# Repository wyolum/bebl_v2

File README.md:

bebl_v2
=======

"Bar End Brake Light" , redux. v2 of Justin's original BEBL with mods.

License
-------
[CERN Open Hardware Licence v1.2 ]

[CERN Open Hardware Licence v1.2 ]:http://www.ohwr.org/attachments/2388/cern_ohl_v_1_2.txt

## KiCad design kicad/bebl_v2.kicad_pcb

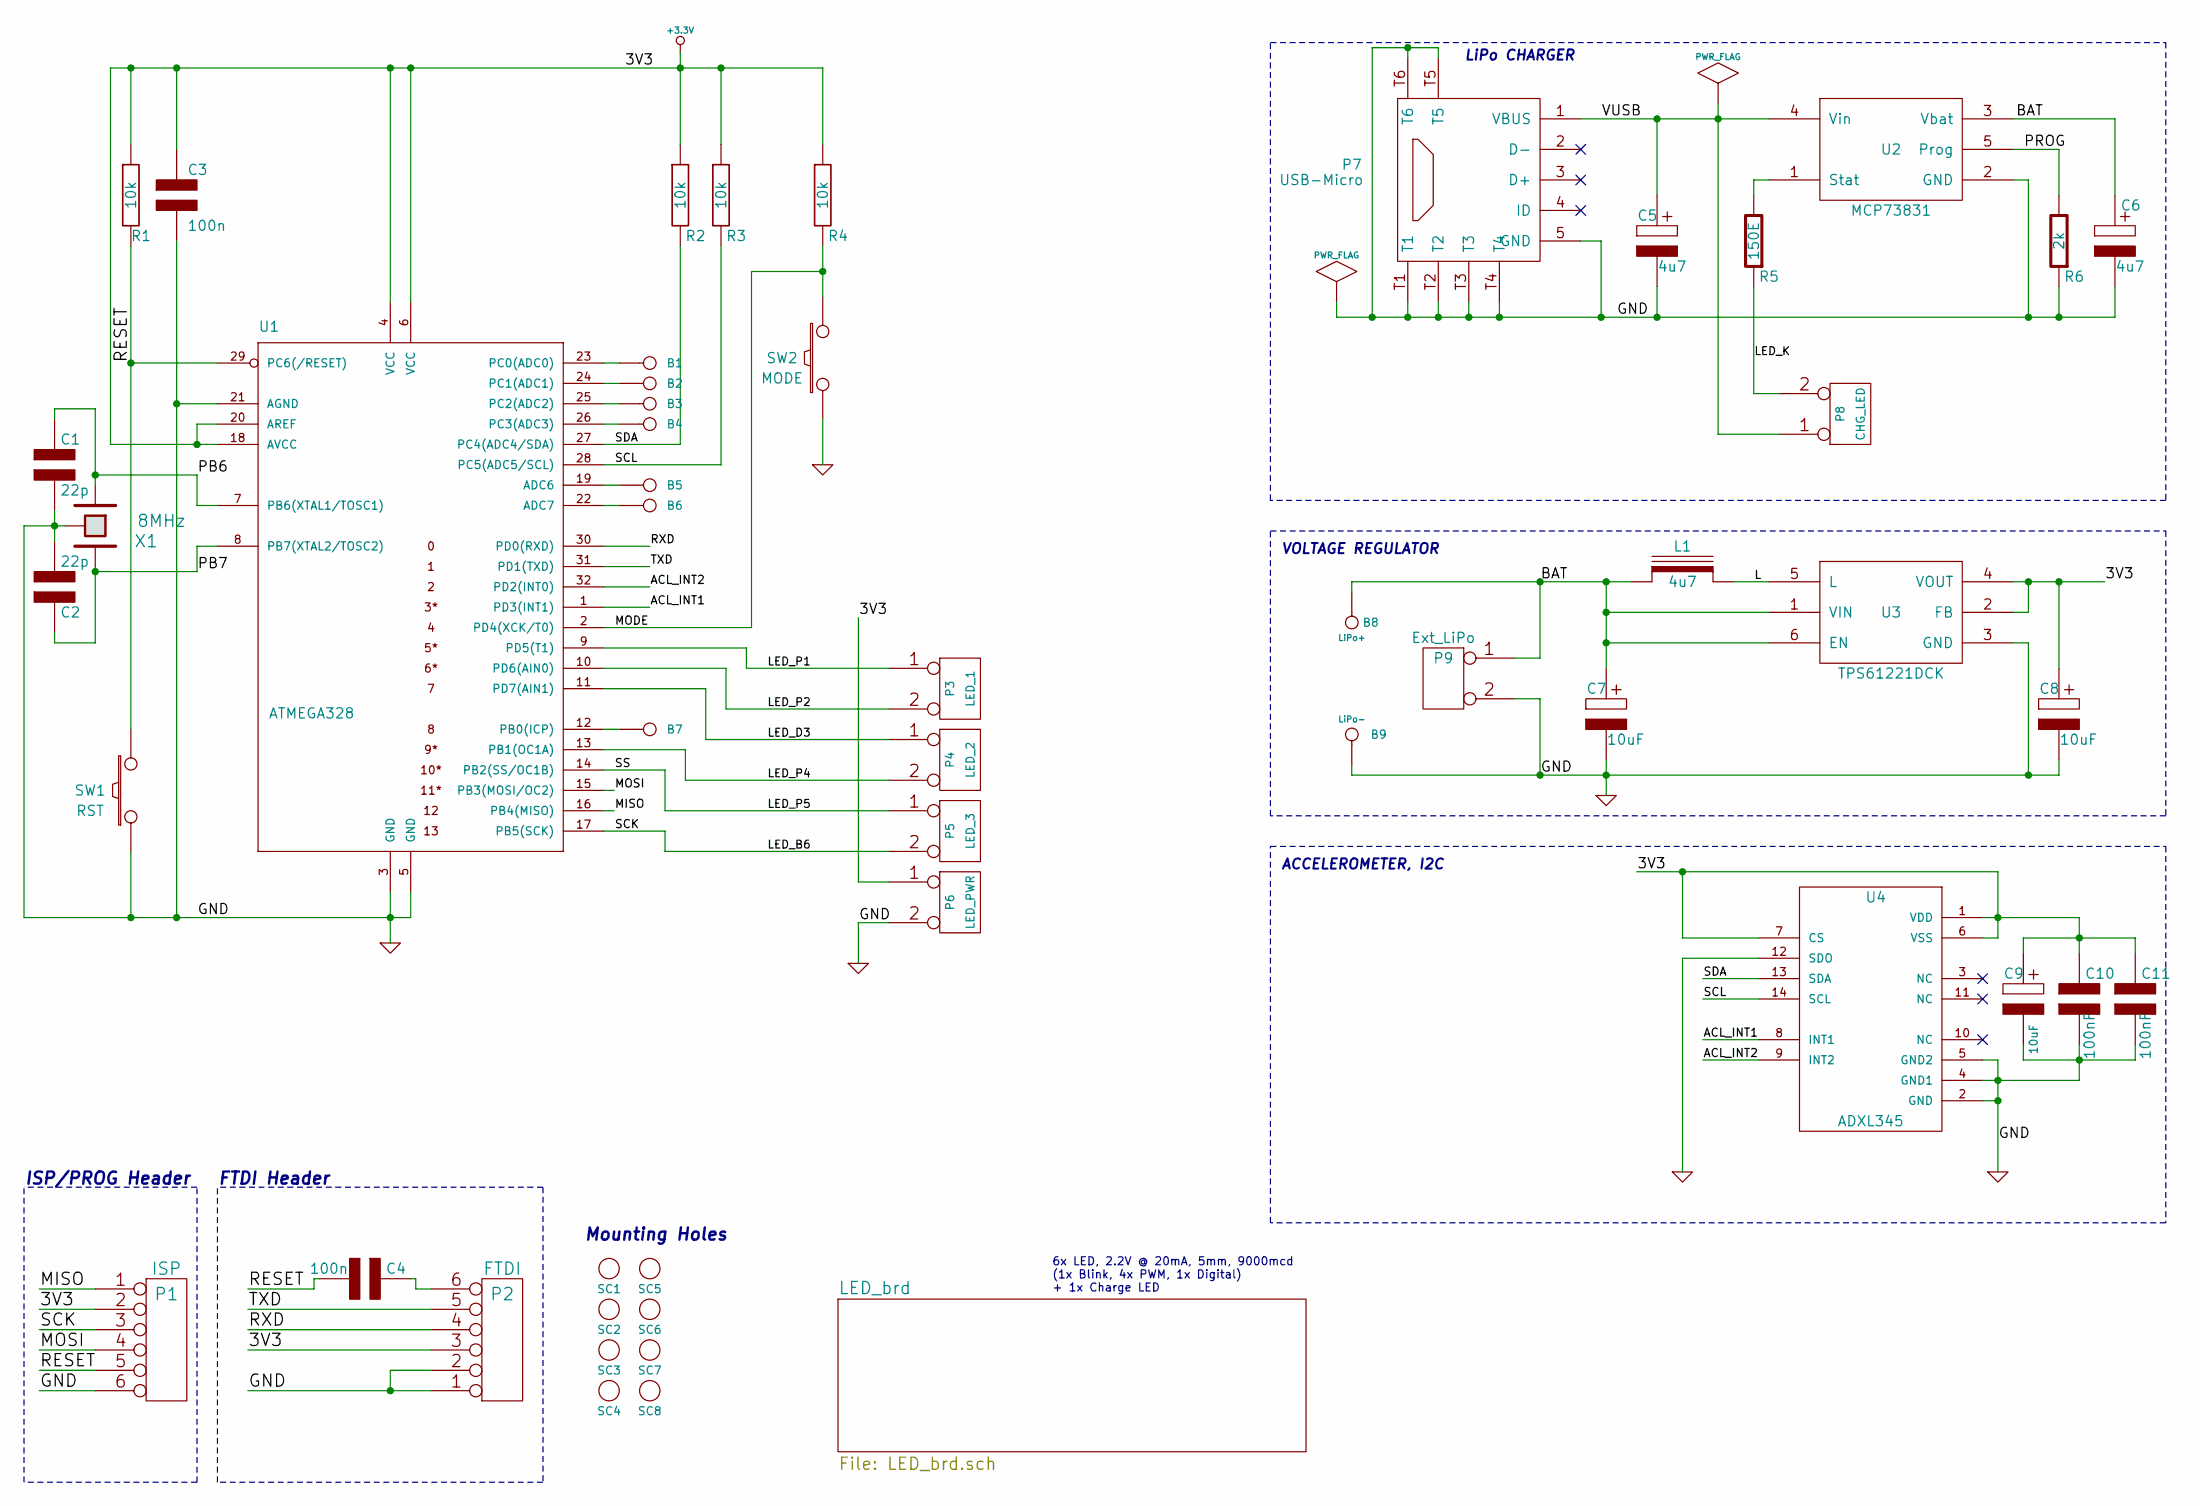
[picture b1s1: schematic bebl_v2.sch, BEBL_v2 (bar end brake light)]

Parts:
B1, B2, B3, B4, B5, B6, B7: I/O; breakout_smd
B8: LiPo+; batt_clip
B9: LiPo-; batt_clip
C1, C2: 22p; c_0805; Digikey 490-1734-1-ND
C3, C4: 100n; c_0805
C5, C6: 4u7; c_0805
C7, C8, C9: 10uF; c_0805
C10, C11: 100nF; c_0805
L1: 4u7; Inductor_LQH3NPN
P1: ISP; Header_3x2_ISP
P2: FTDI; PIN_ARRAY-6X1
P3: LED_1; pin_socket_2
P4: LED_2; pin_socket_2
P5: LED_3; pin_socket_2
P6: LED_PWR; pin_socket_2
P7: USB-Micro; USB_B_Micro
P8: CHG_LED; pin_socket_2
P9: Ext_LiPo; pin_socket_2
R1, R2, R3, R4: 10k; r_0805
R5: 150E; r_0805
R6: 2k; r_0805
SC1, SC2, SC3, SC4, SC5, SC6, SC7, SC8: SCREW; screw_3mm
SW1: RST; Switch_SMT
SW2: MODE; Switch_SMT
U1: ATMEGA328; TQFP32
U2: MCP73831; SOT23-5
U3: TPS61221DCK; SOT23-6_LDO
U4: ADXL345
X1: 8MHz; Xtal_SMD4

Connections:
+3.3V: C3.1, C8.1, C9.1, C10.1, C11.1, P1.2, P2.3, P6.1, R1.1, R2.1, R3.1, R4.1, U1.4 (VCC), U1.6 (VCC), U1.18 (AVCC), U1.20 (AREF), U3.2 (FB), U3.4 (VOUT), U4.1 (VDD), U4.6 (VSS), U4.7 (CS)
/ACL_INT1: U1.1 (PD3(INT1)), U4.8 (INT1)
/ACL_INT2: U1.32 (PD2(INT0)), U4.9 (INT2)
/BAT: B8.1, C6.1, C7.1, L1.1, P9.1, U2.3 (Vbat), U3.1 (VIN), U3.6 (EN)
/L: L1.2, U3.5 (L)
/LED_B6: P1.3, P5.2 (PM), U1.17 (PB5(SCK))
/LED_D3: P4.1, U1.11 (PD7(AIN1))
/LED_K: P8.2 (PM), R5.1
/LED_P1: P3.1, U1.9 (PD5(T1))
/LED_P2: P3.2 (PM), U1.10 (PD6(AIN0))
/LED_P4: P4.2 (PM), U1.13 (PB1(OC1A))
/LED_P5: P5.1, U1.14 (PB2(SS/OC1B))
/MISO: P1.1, U1.16 (PB4(MISO))
/MODE: R4.2, SW2.2, U1.2 (PD4(XCK/T0))
/MOSI: P1.4, U1.15 (PB3(MOSI/OC2))
/PB6: C1.1, U1.7 (PB6(XTAL1/TOSC1)), X1.1
/PROG: R6.2, U2.5 (Prog)
/RESET: C4.2, P1.5, R1.2, SW1.2, U1.29 (PC6(/RESET))
/RXD: P2.4, U1.30 (PD0(RXD))
/SCL: R3.2, U1.28 (PC5(ADC5/SCL)), U4.14 (SCL)
/SDA: R2.2, U1.27 (PC4(ADC4/SDA)), U4.13 (SDA)
/TXD: P2.5, U1.31 (PD1(TXD))
/VUSB: C5.1, P7.1 (VBUS), P8.1, U2.4 (Vin)
unnamed: B1.1, U1.23 (PC0(ADC0))
unnamed: B2.1, U1.24 (PC1(ADC1))
unnamed: B3.1, U1.25 (PC2(ADC2))
unnamed: B4.1, U1.26 (PC3(ADC3))
unnamed: B5.1, U1.19 (ADC6)
unnamed: B6.1, U1.22 (ADC7)
unnamed: B7.1, U1.12 (PB0(ICP))
unnamed: C4.1, P2.6
unnamed: R5.2, U2.1 (Stat)

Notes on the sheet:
FTDI Header
ISP/PROG Header
Mounting Holes
ACCELEROMETER, I2C
VOLTAGE REGULATOR
LiPo CHARGER
6x LED, 2.2V @ 20mA, 5mm, 9000mcd (1x Blink, 4x PWM, 1x Digital) + 1x Charge LED

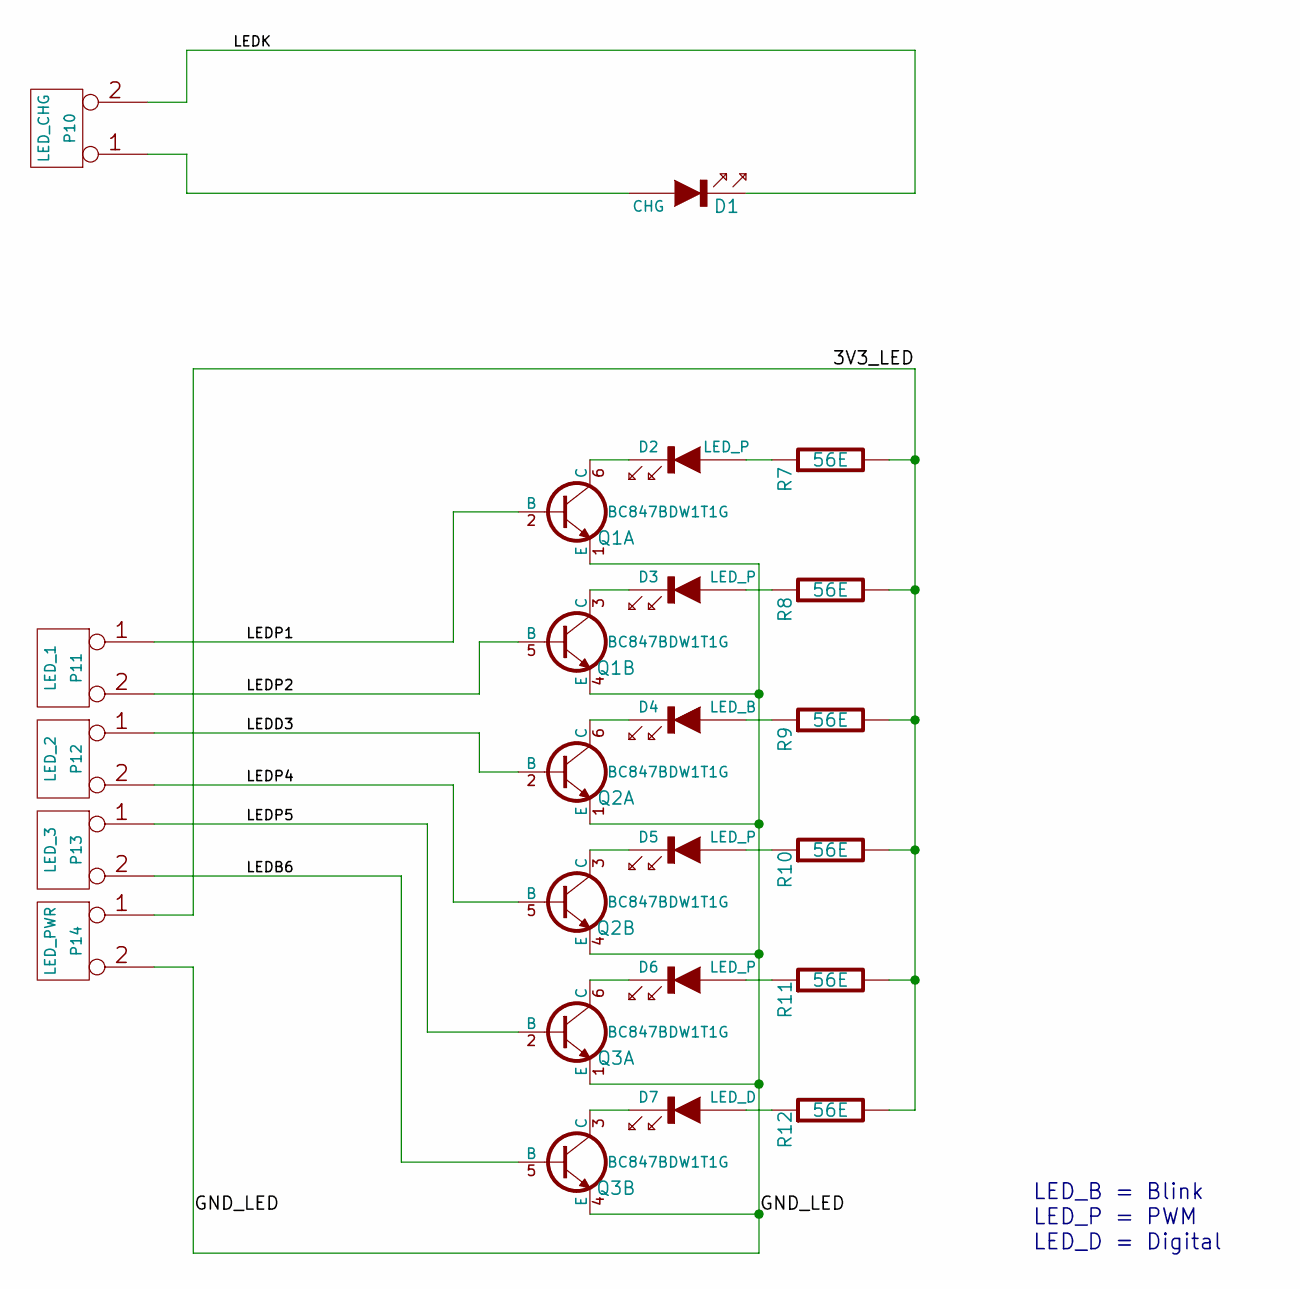
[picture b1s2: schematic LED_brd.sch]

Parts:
D1: CHG; LED-0805
D2, D3, D5, D6: LED_P; LED-5MM
D4: LED_B; LED-5MM
D7: LED_D; LED-5MM
P10: LED_CHG; pin_strip_2
P11: LED_1; pin_strip_2
P12: LED_2; pin_strip_2
P13: LED_3; pin_strip_2
P14: LED_PWR; pin_strip_2
Q1, Q2, Q3: BC847BDW1T1G; SOT23-6
R7, R8, R9, R10, R11, R12: 56E; r_0805

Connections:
/LED_brd/3V3_LED: P14.1, R7.2, R8.2, R9.2, R10.2, R11.2, R12.2
/LED_brd/GND_LED: P14.2 (PM), Q1.1 (E), Q1.4 (E), Q2.1 (E), Q2.4 (E), Q3.1 (E), Q3.4 (E)
/LED_brd/LEDB6: P13.2 (PM), Q3.5 (B)
/LED_brd/LEDD3: P12.1, Q2.2 (B)
/LED_brd/LEDK: D1.2 (K), P10.2 (PM)
/LED_brd/LEDP1: P11.1, Q1.2 (B)
/LED_brd/LEDP2: P11.2 (PM), Q1.5 (B)
/LED_brd/LEDP4: P12.2 (PM), Q2.5 (B)
/LED_brd/LEDP5: P13.1, Q3.2 (B)
unnamed: D1.1 (A), P10.1
unnamed: D2.1 (A), R7.1
unnamed: D2.2 (K), Q1.6 (C)
unnamed: D3.1 (A), R8.1
unnamed: D3.2 (K), Q1.3 (C)
unnamed: D4.1 (A), R9.1
unnamed: D4.2 (K), Q2.6 (C)
unnamed: D5.1 (A), R10.1
unnamed: D5.2 (K), Q2.3 (C)
unnamed: D6.1 (A), R11.1
unnamed: D6.2 (K), Q3.6 (C)
unnamed: D7.1 (A), R12.1
unnamed: D7.2 (K), Q3.3 (C)

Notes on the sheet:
LED_B = Blink LED_P = PWM LED_D = Digital

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
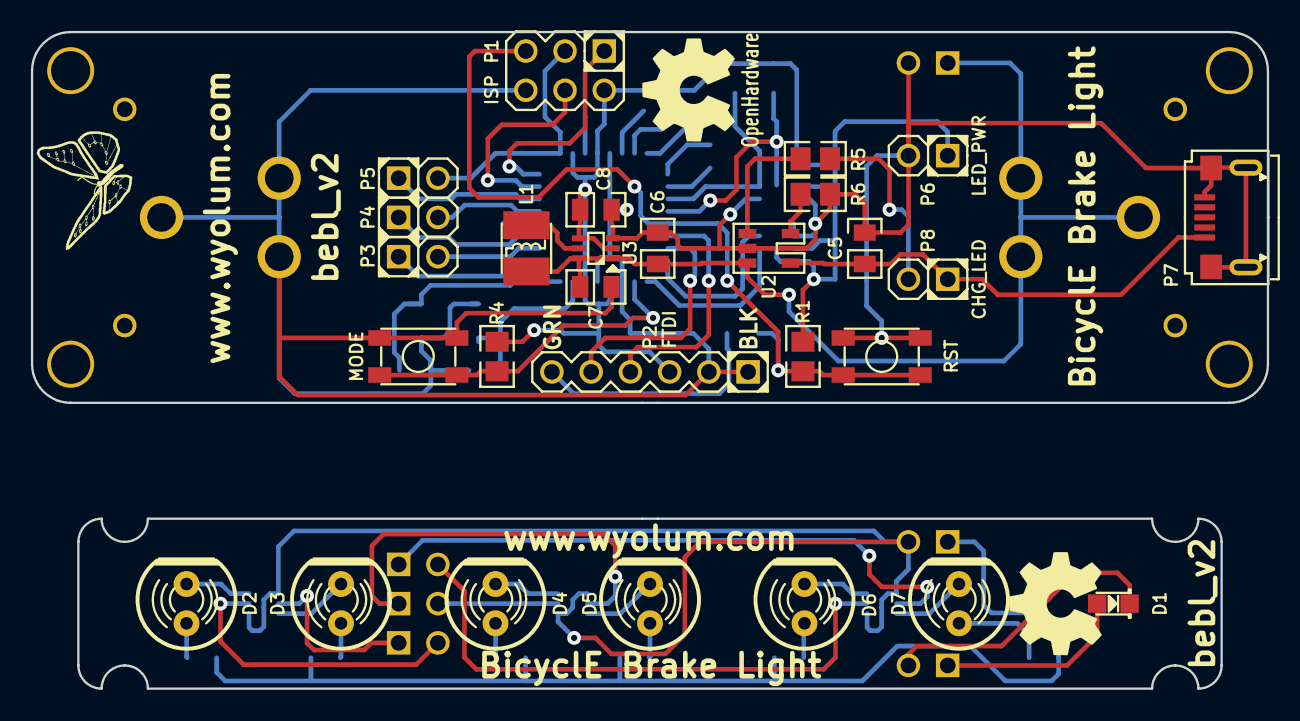
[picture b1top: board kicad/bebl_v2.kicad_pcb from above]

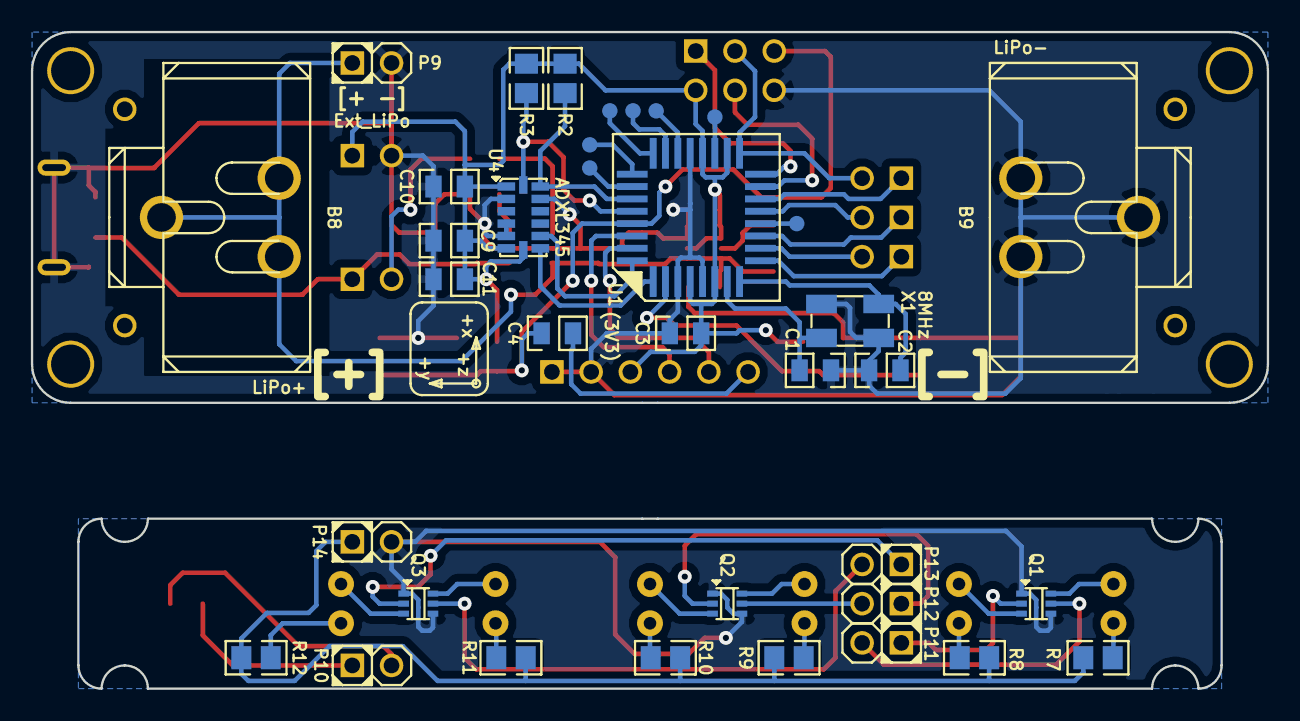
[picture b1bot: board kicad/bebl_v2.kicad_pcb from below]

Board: 2 copper layers, 80.0 x 42.5 mm, 73 parts (36 on the bottom side), 56 nets.

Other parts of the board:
G1: Logo-WL3

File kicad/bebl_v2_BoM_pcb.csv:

"Id";"Designator";"Package";"Quantity";"Designation";"Supplier and ref";
1;"P10";"pin_strip_2";1;"LED_CHG";;;
2;"P8";"pin_socket_2";1;"CHG_LED";;;
3;"P12";"pin_strip_2";1;"LED_2";;;
4;"P14";"pin_strip_2";1;"LED_PWR";;;
5;"P4";"pin_socket_2";1;"LED_2";;;
6;"P3";"pin_socket_2";1;"LED_1";;;
7;"SC8,SC7,SC6,SC5,SC1,SC2,SC3,SC4";"screw_3mm";8;"SCREW";;;
8;"R8,R7,R9,R10,R11,R12";"r_0805";6;"22E";;;
9;"C1,C2";"c_0805";2;"22p";;;
10;"C3,C4";"c_0805";2;"100n";;;
11;"C7,C9,C8";"c_0805";3;"10uF";;;
12;"C5,C6";"c_0805";2;"4u7";;;
13;"C11,C10";"c_0805";2;"100nF";;;
14;"D7";"LED-5MM";1;"LED_B";;;
15;"D6,D5,D3,D2";"LED-5MM";4;"LED_P";;;
16;"D4";"LED-5MM";1;"LED_D";;;
17;"D1";"LED-0805";1;"CHG";;;
18;"L1";"Inductor_LQH3NPN";1;"4u7";;;
19;"P2";"PIN_ARRAY-6X1";1;"FTDI";;;
20;"R4,R2,R3,R1";"r_0805";4;"10k";;;
21;"R5";"r_0805";1;"150E";;;
22;"R6";"r_0805";1;"2k";;;
23;"SW1";"Switch_SMT";1;"RST";;;
24;"U1";"TQFP32";1;"ATMEGA328";;;
25;"U4";"ADXL345";1;"ADXL345";;;
26;"U3";"SOT23-6_LDO";1;"TPS61221DCK";;;
27;"X1";"Xtal_SMD4";1;"8MHz";;;
28;"B1,B2,B3,B4,B5,B6,B7";"breakout_smd";7;"I/O";;;
29;"P1";"Header_3x2_ISP";1;"ISP";;;
30;"P5";"pin_socket_2";1;"LED_3";;;
31;"P6";"pin_socket_2";1;"LED_PWR";;;
32;"P9";"pin_socket_2";1;"Ext_LiPo";;;
33;"P13";"pin_strip_2";1;"LED_3";;;
34;"P11";"pin_strip_2";1;"LED_1";;;
35;"SW2";"Switch_SMT";1;"MODE";;;
36;"G***,G***";"OSHW_6mm";2;"LOGO";;;
37;"G1";"Logo-WL3";1;"Logo-WL3";;;
38;"U2";"SOT23-5";1;"MCP73831";;;
39;"Q1,Q2,Q3";"SOT363";3;"BC847BDW1T1G";;;
40;"B9";"batt_clip";1;"LiPo-";;;
41;"B8";"batt_clip";1;"LiPo+";;;
42;"P7";"USB_B_Micro_seeed";1;"USB-Micro";;;

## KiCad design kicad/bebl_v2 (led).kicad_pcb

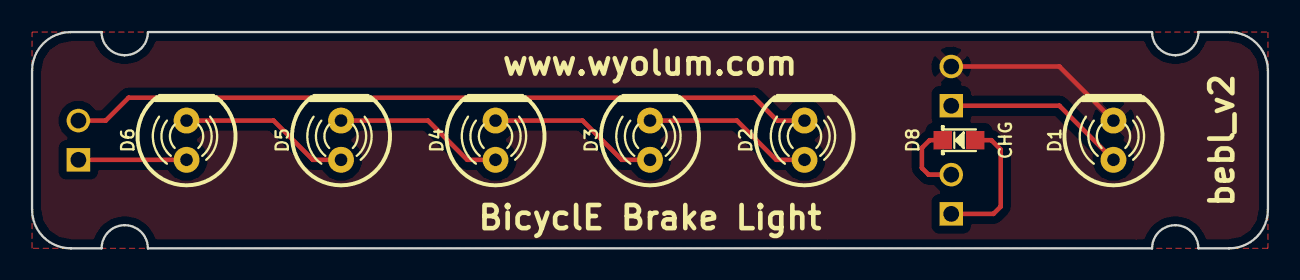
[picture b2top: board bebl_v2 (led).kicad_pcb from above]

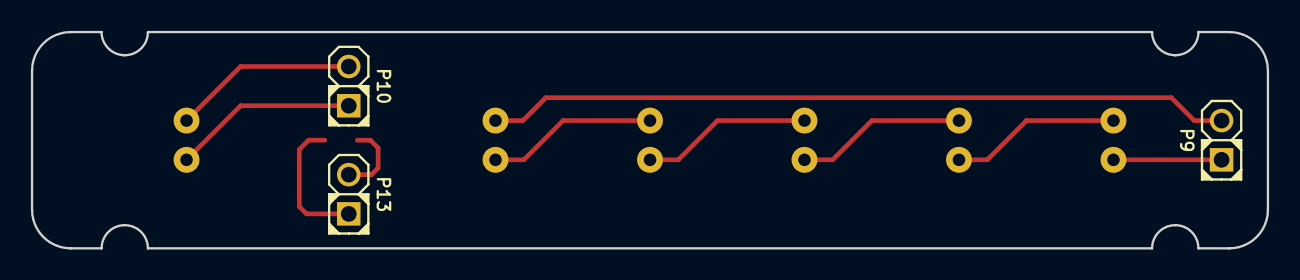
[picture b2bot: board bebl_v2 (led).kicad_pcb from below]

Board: 2 copper layers, 80.0 x 14.0 mm, 10 parts (3 on the bottom side), 10 nets.

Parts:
D1: DRL; LED-5MM
D2, D3, D4, D5, D6: LED_R; LED-5MM
D8: CHG; LED-0805
P9: LED_DRV; pin_strip_2
P10: LED_DRL; pin_strip_2
P13: LED_CHG; pin_strip_2

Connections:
/ANOD: D6.1, P9.1
/CATH: D2.2, P9.2
/D1A: D1.1, P10.1
/D1K: D1.2, P10.2
unnamed: D2.1, D3.2
unnamed: D3.1, D4.2
unnamed: D4.1, D5.2
unnamed: D5.1, D6.2
unnamed: D8.1, P13.1
unnamed: D8.2, P13.2

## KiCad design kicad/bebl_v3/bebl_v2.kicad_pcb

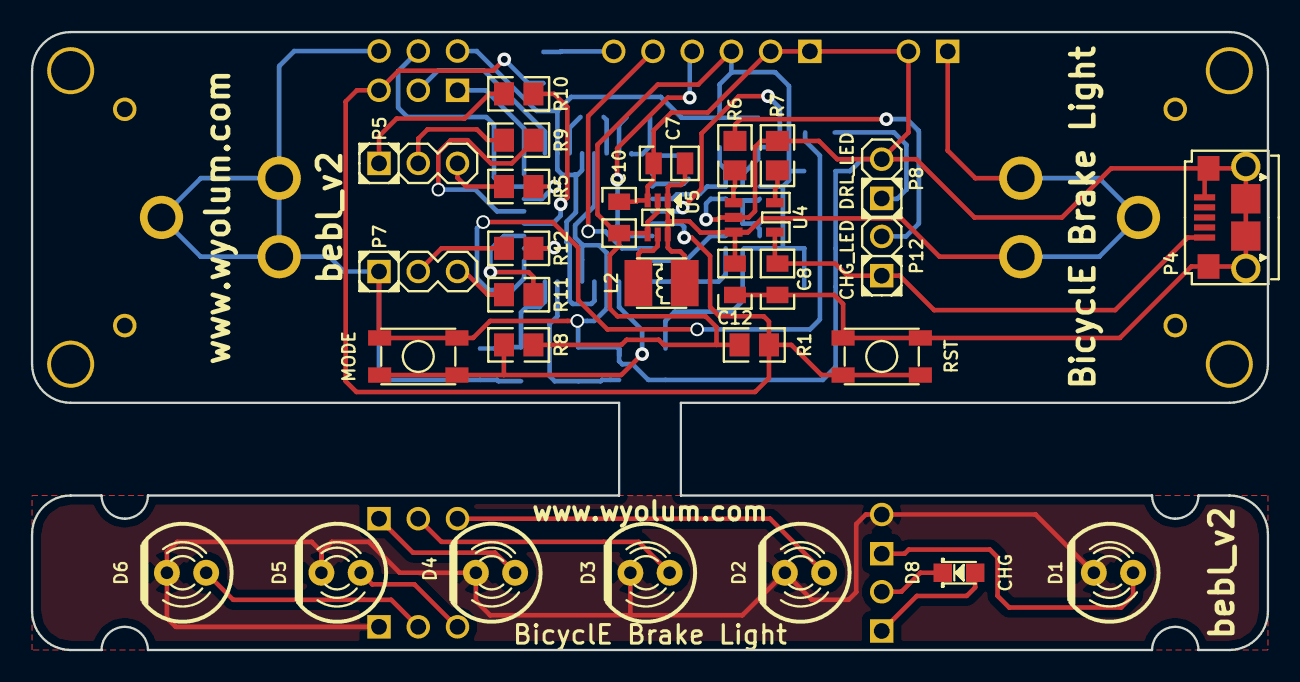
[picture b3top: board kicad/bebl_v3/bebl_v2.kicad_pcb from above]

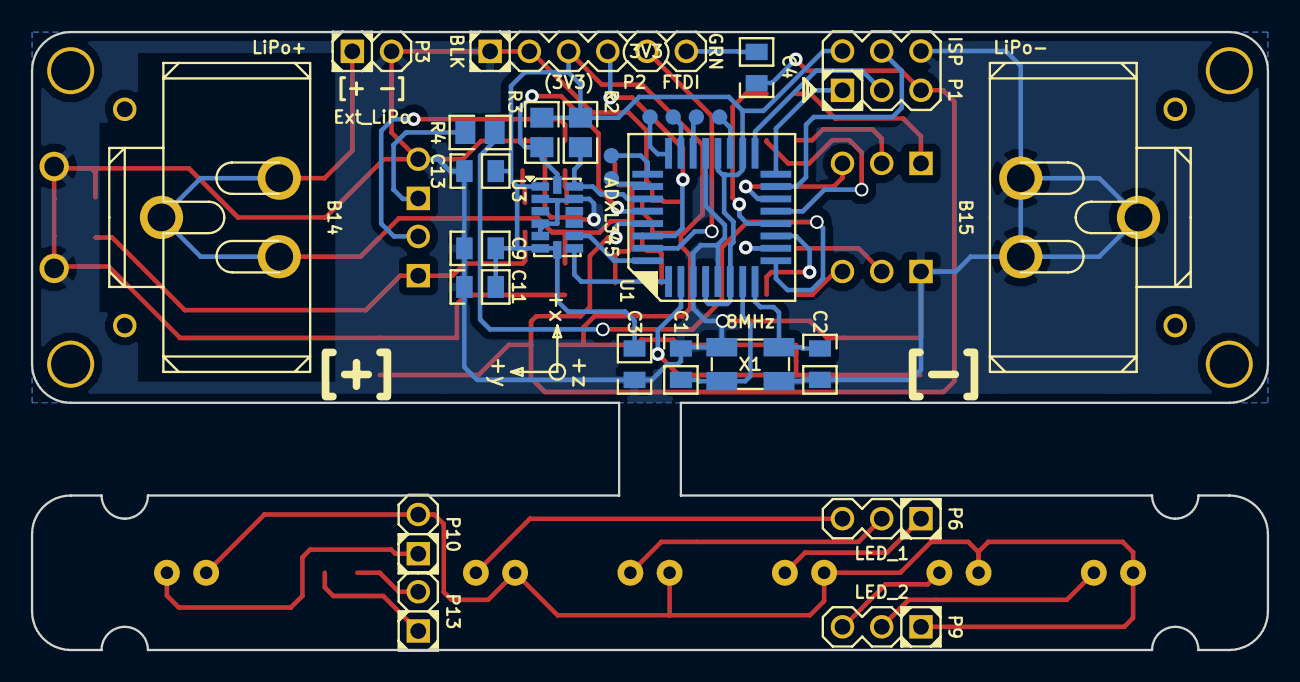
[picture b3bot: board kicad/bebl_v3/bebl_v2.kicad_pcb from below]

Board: 2 copper layers, 80.0 x 40.0 mm, 66 parts (28 on the bottom side), 49 nets.

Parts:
B1, B2, B3, B4, B5, B6: I/O; breakout_smd
B14: LiPo+; batt_clip
B15: LiPo-; batt_clip
C1, C2: 22p; c_0805
C3, C4: 100n; c_0805
C7, C9, C10: 10uF; c_0805
C8, C12: 4u7; c_0805
C11, C13: 100nF; c_0805
D1: DRL; LED-5MM
D2, D3, D4, D5, D6: LED_R; LED-5MM
D8: CHG; LED-0805
L2: 4u7; Inductor_LQH3NPN
P1: ISP; Header_3x2_ISP
P2: FTDI; PIN_ARRAY-6X1
P3: Ext_LiPo; pin_strip_2
P4: USB-Micro; USB_B_Micro
P5: DRV_1; pin_socket_3
P6: LED_1; PIN_ARRAY-3X1
P7: DRV_2; pin_socket_3
P8: DRL_LED; pin_socket_2
P9: LED_2; PIN_ARRAY-3X1
P10: LED_DRL; pin_strip_2
P12: CHG_LED; pin_socket_2
P13: LED_CHG; pin_strip_2
R1, R2, R3, R8: 10k; r_0805
R4, R5, R9, R10, R11, R12: 55E; r_0805
R6: 150E; r_0805
R7: 2k; r_0805
SC1, SC2, SC3, SC4, SC5, SC6, SC7, SC8: SCREW; screw_3mm
SW1: RST; Switch_SMT
SW2: MODE; Switch_SMT
U1: ATMEGA328; TQFP32
U3: ADXL345
U4: MCP73831; SOT23-5
U5: TPS61221DCK; SOT23-6_LDO
X1: 8MHz; Xtal_SMD4

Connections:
+3.3V: C3.1, C9.1, C10.1, C11.1, C13.1, P1.2, P2.3, R1.1, R2.1, R3.1, R8.1, U1.4, U1.6, U1.18, U1.20, U3.1, U3.6, U3.7, U5.2, U5.4
/ACL_INT1: U1.1, U3.8
/ACL_INT2: U1.32, U3.9
/BAT: B14.1, C7.1, C12.1, L2.1, P3.1, U4.3, U5.1, U5.6
/D1A: D1.1, P10.1
/DRL: P8.1, R4.1
/L: L2.2, U5.5
/LED_D1: R4.2, U1.9
/LED_D2: R5.2, U1.14
/LED_D3: R9.2, U1.13
/LED_D4: R10.2, U1.12
/LED_D5: R11.2, U1.11
/LED_D6: R12.2, U1.10
/LED_GND: D1.2, D2.2, D3.2, D4.2, D5.2, D6.2, P9.1, P10.2
/MISO: P1.1, U1.16
/MODE: R8.2, SW2.2, U1.2
/MOSI: P1.4, U1.15
/PB6: C1.1, U1.7, X1.1
/PB7: C2.2, U1.8, X1.2
/PROG: R7.2, U4.5
/RESET: C4.2, P1.5, R1.2, SW1.2, U1.29
/RXD: P2.4, U1.30
/SCK: P1.3, U1.17
/SCL: R3.2, U1.28, U3.14
/SDA: R2.2, U1.27, U3.13
/TXD: P2.5, U1.31
/VUSB: C8.1, P4.1, P12.1, U4.4
GND: B15.1, C1.2, C2.1, C3.2, C7.2, C8.2, C9.2, C10.2, C11.2, C12.2, C13.2, P1.6, P2.1, P2.2, P3.2, P4.5, P4.T1, P4.T2, P4.T3, P4.T4, P4.T5, P4.T6, P7.1, P8.2, R7.1, SW1.1, SW2.1, U1.3, U1.5, U1.21, U3.2, U3.4, U3.5, U3.12, U4.2, U5.3, X1.3
unnamed: B1.1, U1.23
unnamed: B2.1, U1.24
unnamed: B3.1, U1.25
unnamed: B4.1, U1.26
unnamed: B5.1, U1.19
unnamed: B6.1, U1.22
unnamed: C4.1, P2.6
unnamed: D2.1, P6.3
unnamed: D3.1, P6.2
unnamed: D4.1, P6.1
unnamed: D5.1, P9.3
unnamed: D6.1, P9.2
unnamed: D8.1, P13.1
unnamed: D8.2, P13.2
unnamed: P5.1, R10.1
unnamed: P5.2, R9.1
unnamed: P5.3, R5.1
unnamed: P7.2, R12.1
unnamed: P7.3, R11.1
unnamed: P12.2, R6.1
unnamed: R6.2, U4.1

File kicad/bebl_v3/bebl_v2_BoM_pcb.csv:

Id,Designator,Package,Quantity,Designation,Supplier and ref
1,B14,bebl_v2_pretty:batt_clip,1,LiPo+,
2,B15,bebl_v2_pretty:batt_clip,1,LiPo-,
3,P13,bebl_v2_pretty:pin_strip_2,1,LED_CHG,
4,P12,bebl_v2_pretty:pin_socket_2,1,CHG_LED,
5,P9,bebl_v2_pretty:pin_strip_2,1,LED_DRV,
6,P10,bebl_v2_pretty:pin_strip_2,1,LED_DRL,
7,P11,bebl_v2_pretty:pin_socket_2,1,DRV_LED,
8,P8,bebl_v2_pretty:pin_socket_2,1,DRL_LED,
9,"SC8,SC7,SC6,SC5,SC1,SC2,SC3,SC4",bebl_v2_pretty:screw_3mm,8,SCREW,
10,SW2,bebl_v2_pretty:Switch_SMT,1,MODE,
11,"R8,R1,R2,R3",bebl_v2_pretty:r_0805,4,10k,RMCF0805FT10K0CT-ND
12,"C1,C2",bebl_v2_pretty:c_0805,2,22p,
13,"C3,C4",bebl_v2_pretty:c_0805,2,100n,CL21B104KACNNNC
14,"C5,C7,C9,C10",bebl_v2_pretty:c_0805,4,10uF,
15,C6,bebl_v2_pretty:c_0805,1,1uF,
16,"C8,C12",bebl_v2_pretty:c_0805,2,4u7,
17,"C11,C13",bebl_v2_pretty:c_0805,2,100nF,
18,D1,bebl_v2_pretty:LED-5MM,1,DRL,
19,"D2,D3,D4,D5,D6",bebl_v2_pretty:LED-5MM,5,LED_R,
20,D7,bebl_v2_pretty:Diode-EMD2,1,RB520S-30TE61,
21,D8,bebl_v2_pretty:LED-0805,1,CHG,
22,L1,bebl_v2_pretty:Inductor_NLCV32,1,10uH,
23,L2,bebl_v2_pretty:Inductor_LQH3NPN,1,4u7,
24,P2,bebl_v2_pretty:PIN_ARRAY-6X1,1,FTDI,
25,P4,bebl_v2_pretty:USB_B_Micro,1,USB-Micro,
26,R4,bebl_v2_pretty:r_0805,1,140E,
27,R5,bebl_v2_pretty:r_0805,1,12.4E,
28,R6,bebl_v2_pretty:r_0805,1,150E,
29,R7,bebl_v2_pretty:r_0805,1,2k,
30,SW1,bebl_v2_pretty:Switch_SMT,1,RST,
31,U1,bebl_v2_pretty:TQFP32,1,ATMEGA328,ATMEGA328P-AU
32,U2,bebl_v2_pretty:SOT23-6,1,FAN5346,
33,U3,bebl_v2_pretty:ADXL345,1,ADXL345,
34,U4,bebl_v2_pretty:SOT23-5,1,MCP73831,
35,U5,bebl_v2_pretty:SOT23-6_LDO,1,TPS61221DCK,
36,X1,bebl_v2_pretty:Xtal_SMD4,1,8MHz,
37,P3,bebl_v2_pretty:pin_strip_2,1,Ext_LiPo,
38,"B1,B2,B3,B4,B5,B6,B10,B11,B12,B13",bebl_v2_pretty:breakout_smd,10,I/O,
39,P1,bebl_v2_pretty:Header_3x2_ISP,1,ISP,

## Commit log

2014-09-14 bebl_v2 initial commit
2014-09-14 bebl_v2 work in progress
2014-10-13 LED driver reference circuits added
2014-10-21 work in progress
2014-10-26 bebl_v2 initial 3d mockup
2014-10-27 bebl_v2 3d mockup of 2 separate boards
2014-10-28 working on case for bebl_v2
2014-10-28 bebl_v2 3d of housing, work in progress
2014-10-29 bebl_v2 track layout, work in progress
2014-10-30 bebl_v2 track layout, almost done
2014-10-30 created new wedge piece with SP cutout.
2014-10-30 jwedge update
2014-10-31 minor tweeks to jwedge
2014-11-01 bebl_v2 box stl files ready for prototype
2014-11-02 made an alternative back cover that does not need to be transparent
2014-11-03 modified justins version of top cover
2014-11-03 fixed led placement
2014-11-03 fixed jcover fillet_r and led placement
2014-11-03 bebl_v2 added new lens cover
2014-11-03 bebl_v2 minor update
2014-11-04 changed fillet radius on jwedge
2014-11-11 minor update
2014-11-13 BoM modified
2014-11-14 direct LED drive version, work in progress
2014-11-15 revised layout for driverless version, in folder bebl_v3. Work in progress
2014-11-16 revised layout for driverless version, in folder bebl_v3. Check PDF files in GERBER folder
2014-11-16 modified housing drawing
2014-11-18 corrected accel x/y/z markings on silk legend
2014-12-04 working on transistor based driver for leds
2014-12-05 modified schematic for transistor drive
2014-12-10 minor cleanup
2014-12-15 new LED drive circuit, work in progress
2015-01-26 making some progress with new layout
2015-01-29 layout work in progress
2015-01-30 track layout done. Needs verification
2015-01-31 added Justin's local path for 3D files
2015-02-02 made LED board smaller
2015-02-03 bebl_v2 gerbers ready. BoM pending
2015-02-03 footprint errors corrected, BoM ready, but pending seeed format
2015-02-04 still working on BoM
2015-02-05 Ready to prototype. Gerbers generated
2015-03-12 DFM changes to bebl_v2 based on seeed feedback
2015-04-07 first test on actual device
2015-04-08 added ADXL libs
2015-04-08 slowed scan
2015-04-17 got interrupts working kinda
2015-04-19 bebl_v2 housing mods
2015-04-20 sleep mode test program initial commit
2015-04-21 reorganize code for sleep
2015-04-21 top cover CHG led hole thickness reduced
2015-04-22 main box height reduced by 3mm and bottom thickness is 1mm
2015-04-23 main box pcb support pillar height reduced by 1mm
2015-04-24 fresh 3D model extracted from KiCad
2015-04-24 frecad 3d drawing for housing updated
2015-04-24 updated BEBL_test.ino
2015-05-07 some new images added
2015-06-12 added image of bebl housing
2015-12-25 added manual calibration code. Updated filter coeff
2015-12-25 added BEBL.ino
2015-12-26 added lighting code, first functional brakelight. Need to add sleep and wake code: Kevin??
2015-12-26 updated bandwidth of filters after testing failed. new version tested well.
2015-12-27 another road test. Worked great!
2015-12-29 add example with power saving sleep. wake with activity or tap
2015-12-31 integrated Kevin's power off and wake code
2015-12-31 added self calibration routine. hold mode on start up to calibrate, rotate 2x on each axis, then double tap to complete
2015-12-31 added autoloading of cal from eeprom
2018-07-15 added Gerber ZIP
2019-05-09 added board WRL files to fabricate
